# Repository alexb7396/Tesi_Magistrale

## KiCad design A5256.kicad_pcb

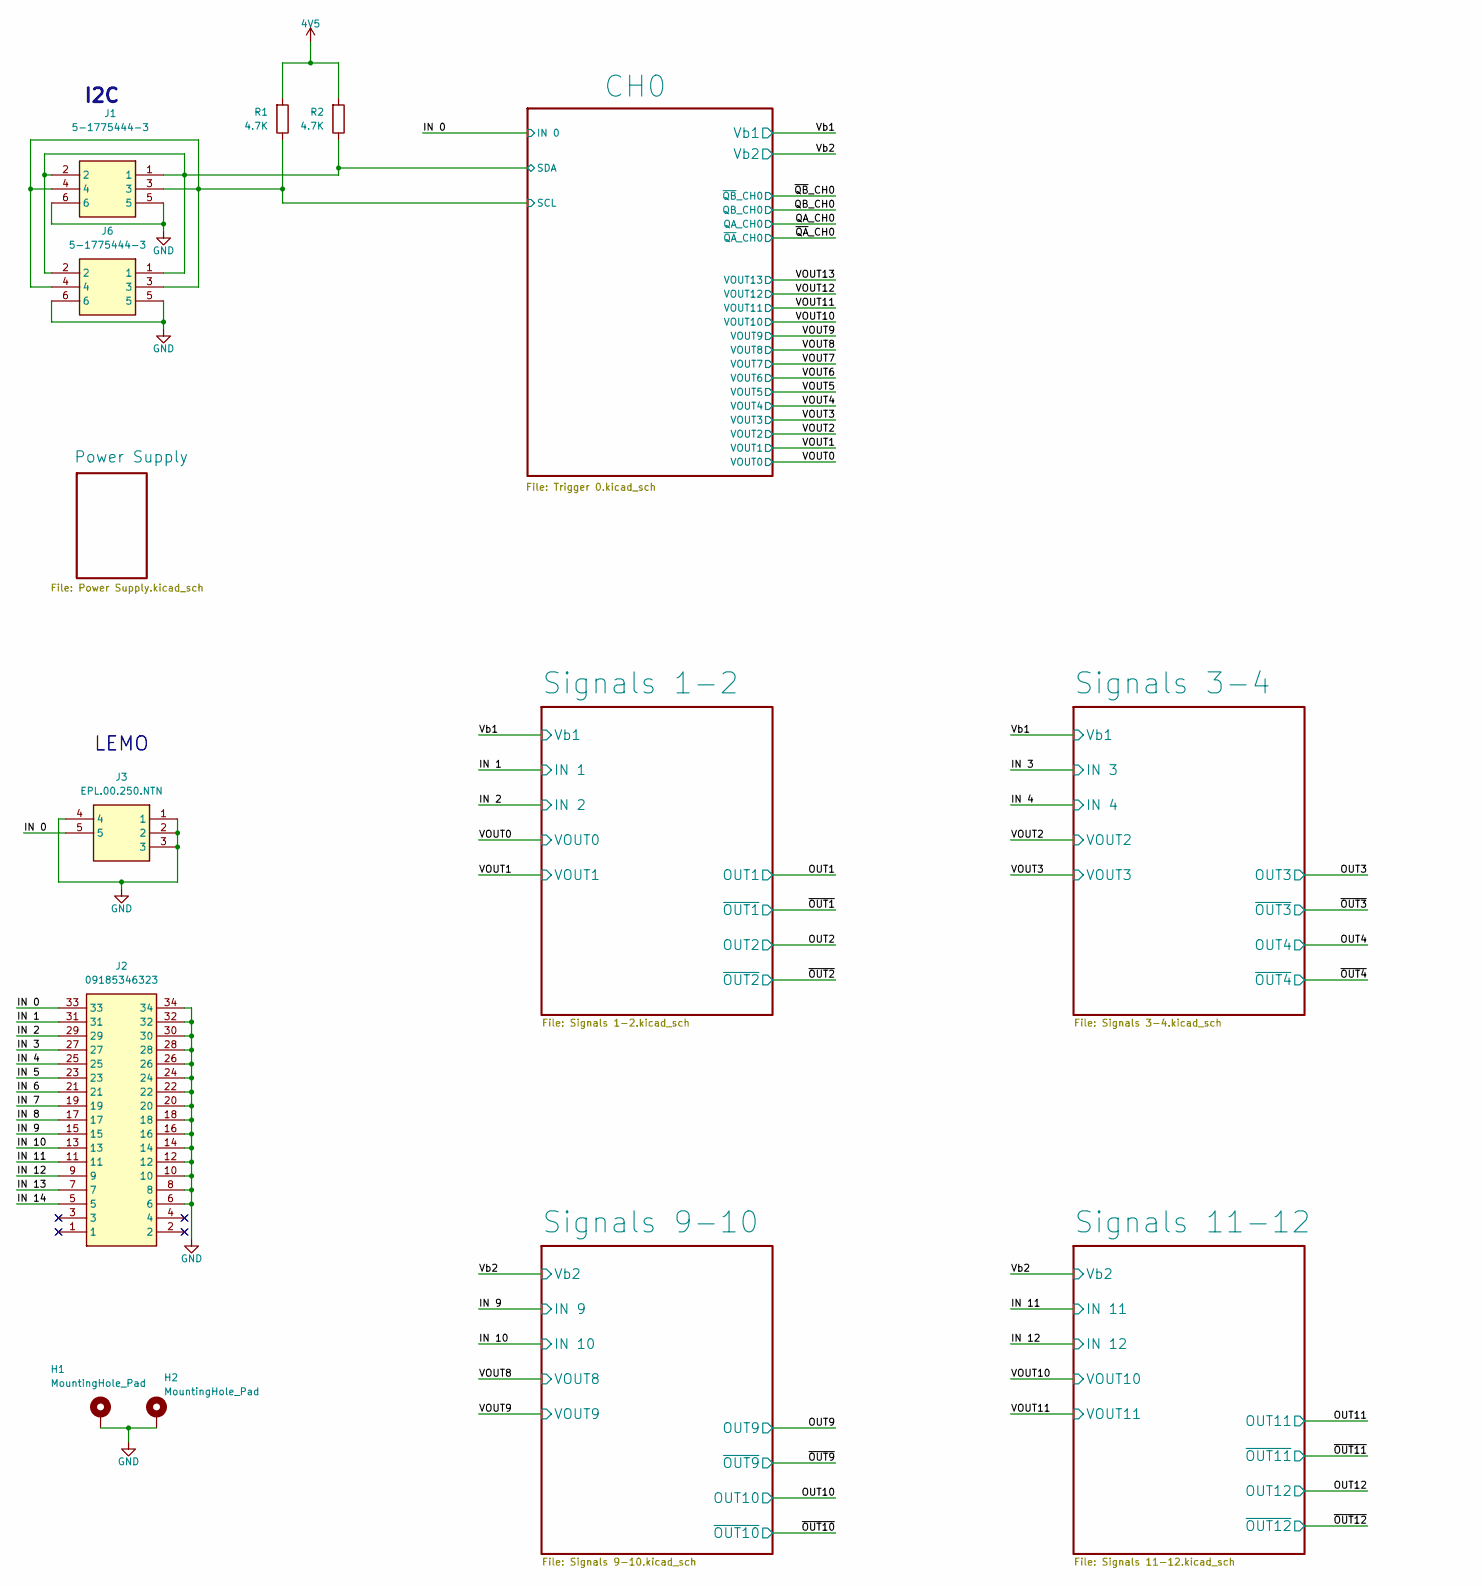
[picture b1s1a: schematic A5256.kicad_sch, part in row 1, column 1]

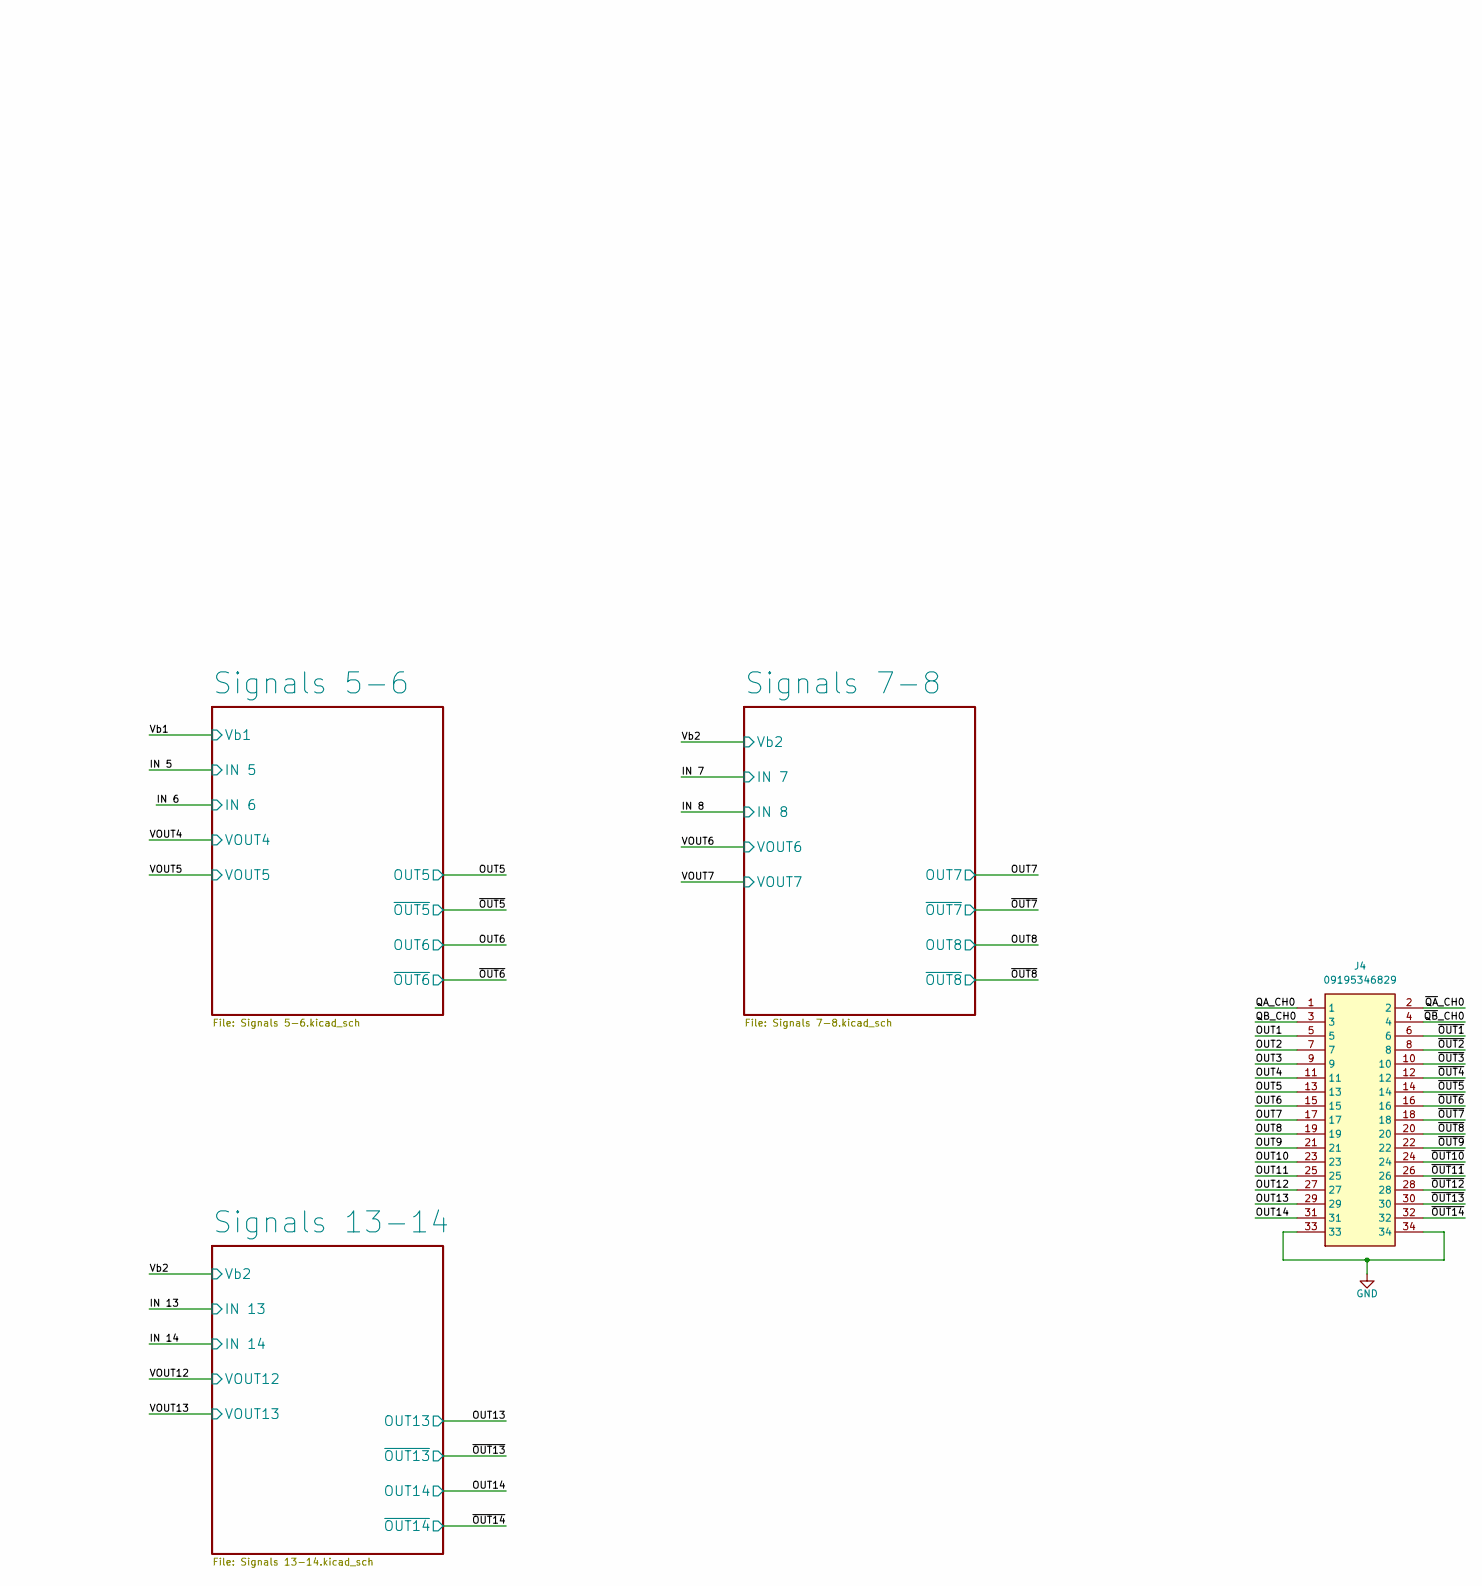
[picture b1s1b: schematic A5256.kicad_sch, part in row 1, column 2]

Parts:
H1, H2: MountingHole_Pad; MountingHole_3mm_Pad_TopBottom
J1, J6: 5-1775444-3; 517754443; Mouser Part Number 571-5-1775444-3
J2: 09185346323; Mouser Part Number 617-09-18-534-6323
J3: EPL.00.250.NTN; LEMO-EPA.00.250.DTN; Mouser Part Number 736-EPL00250NTN
J4: 09195346829; 2x17 Connector; Mouser Part Number 617-09195346829
R1, R2: 4.7K; R_0603_1608Metric_Pad0.98x0.95mm_HandSolder

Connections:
4V5: R1.2, R2.2; also elsewhere on the board
/CH0/SCL: J1.3, J1.4, J6.3, J6.4, R1.1; also elsewhere on the board
/CH0/SDA: J1.1, J1.2, J6.1, J6.2, R2.1; also elsewhere on the board
/IN 0: J2.33, J3.5; also elsewhere on the board
/IN 1: J2.31; also elsewhere on the board
/IN 2: J2.29; also elsewhere on the board
/IN 3: J2.27; also elsewhere on the board
/IN 4: J2.25; also elsewhere on the board
/IN 5: J2.23; also elsewhere on the board
/IN 6: J2.21; also elsewhere on the board
/IN 7: J2.19; also elsewhere on the board
/IN 8: J2.17; also elsewhere on the board
/IN 9: J2.15; also elsewhere on the board
/IN 10: J2.13; also elsewhere on the board
/IN 11: J2.11; also elsewhere on the board
/IN 12: J2.9; also elsewhere on the board
/IN 13: J2.7; also elsewhere on the board
/IN 14: J2.5; also elsewhere on the board
/OUT1: J4.5; also elsewhere on the board
/OUT2: J4.7; also elsewhere on the board
/OUT3: J4.9; also elsewhere on the board
/OUT4: J4.11; also elsewhere on the board
/OUT5: J4.13; also elsewhere on the board
/OUT6: J4.15; also elsewhere on the board
/OUT7: J4.17; also elsewhere on the board
/OUT8: J4.19; also elsewhere on the board
/OUT9: J4.21; also elsewhere on the board
/OUT10: J4.23; also elsewhere on the board
/OUT11: J4.25; also elsewhere on the board
/OUT12: J4.27; also elsewhere on the board
/OUT13: J4.29; also elsewhere on the board
/OUT14: J4.31; also elsewhere on the board
/QA_CH0: J4.1; also elsewhere on the board
/QB_CH0: J4.3; also elsewhere on the board
/~OUT1: J4.6; also elsewhere on the board
/~OUT2: J4.8; also elsewhere on the board
/~OUT3: J4.10; also elsewhere on the board
/~OUT4: J4.12; also elsewhere on the board
/~OUT5: J4.14; also elsewhere on the board
/~OUT6: J4.16; also elsewhere on the board
/~OUT7: J4.18; also elsewhere on the board
/~OUT8: J4.20; also elsewhere on the board
/~OUT9: J4.22; also elsewhere on the board
/~OUT10: J4.24; also elsewhere on the board
/~OUT11: J4.26; also elsewhere on the board
/~OUT12: J4.28; also elsewhere on the board
/~OUT13: J4.30; also elsewhere on the board
/~OUT14: J4.32; also elsewhere on the board
/~QA_CH0: J4.2; also elsewhere on the board
/~QB_CH0: J4.4; also elsewhere on the board
GND: H1.1, H2.1, J1.5, J1.6, J2.6, J2.8, J2.10, J2.12, J2.14, J2.16, J2.18, J2.20, J2.22, J2.24, J2.26, J2.28, J2.30, J2.32, J2.34, J3.1, J3.2, J3.3, J3.4, J4.33, J4.34, J6.5, J6.6; also elsewhere on the board

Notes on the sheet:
I2C
LEMO

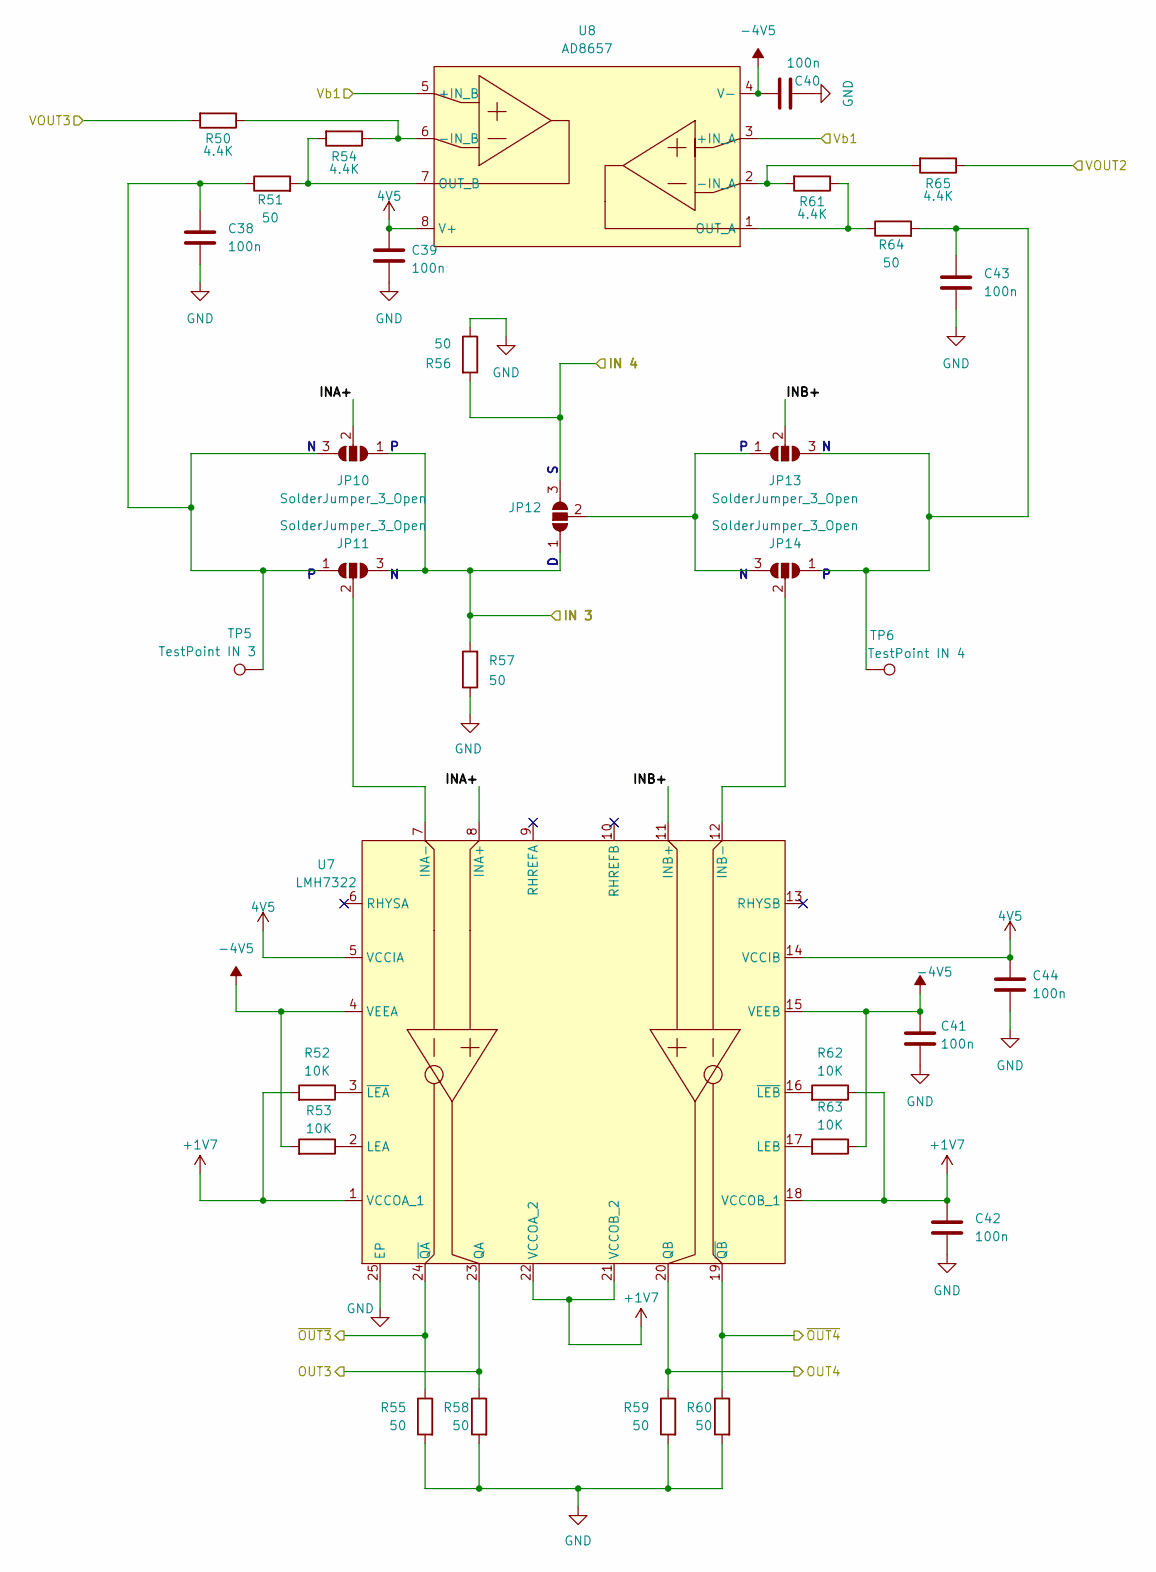
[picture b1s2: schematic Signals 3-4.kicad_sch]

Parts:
C38, C39, C40, C41, C42, C43, C44: 100n; C_0603_1608Metric_Pad1.08x0.95mm_HandSolder
JP10, JP11, JP12, JP13, JP14: SolderJumper_3_Open; SolderJumper-3_P1.3mm_Open_RoundedPad1.0x1.5mm_NumberLabels
R50, R54, R61, R65: 4.4K; R_0603_1608Metric_Pad0.98x0.95mm_HandSolder
R51, R55, R56, R57, R58, R59, R60, R64: 50; R_0603_1608Metric_Pad0.98x0.95mm_HandSolder
R52, R53, R62, R63: 10K; R_0603_1608Metric_Pad0.98x0.95mm_HandSolder
TP5: TestPoint IN 3; TestPoint_Pad_D1.0mm
TP6: TestPoint IN 4; TestPoint_Pad_D1.0mm
U7: LMH7322; QFN50P400X400X80-25N
U8: AD8657; SOP65P490X110-8N

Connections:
4V5: C39.1, C44.1, U7.5 (VCCIA), U7.14 (VCCIB), U8.8 (V+); also elsewhere on the board
+1V7: C42.1, R52.2, R62.1, U7.1 (VCCOA_1), U7.18 (VCCOB_1), U7.21 (VCCOB_2), U7.22 (VCCOA_2); also elsewhere on the board
-4V5: C40.1, C41.1, R53.2, R63.1, U7.4 (VEEA), U7.15 (VEEB), U8.4 (V-); also elsewhere on the board
/IN 3: JP10.1 (A), JP11.3 (B), JP12.1 (A), R57.2; also elsewhere on the board
/IN 4: JP12.3 (B), R56.2; also elsewhere on the board
/OUT3: R58.1, U7.23 (QA); also elsewhere on the board
/OUT4: R59.1, U7.20 (QB); also elsewhere on the board
/Signals 3-4/INA+: JP10.2 (C), U7.8 (INA+)
/Signals 3-4/INB+: JP13.2 (C), U7.11 (INB+)
/VOUT2: R65.1; also elsewhere on the board
/VOUT3: R50.2; also elsewhere on the board
/Vb1: U8.3 (+IN_A), U8.5 (+IN_B); also elsewhere on the board
/~OUT3: R55.1, U7.24 (~QA); also elsewhere on the board
/~OUT4: R60.1, U7.19 (~QB); also elsewhere on the board
GND: C38.2, C39.2, C40.2, C41.2, C42.2, C43.2, C44.2, R55.2, R56.1, R57.1, R58.2, R59.2, R60.2, U7.25 (EP); also elsewhere on the board
unnamed: C38.1, JP10.3 (B), JP11.1 (A), R51.1, TP5.1
unnamed: JP11.2 (C), U7.7 (INA-)
unnamed: JP12.2 (C), JP13.1 (A), JP14.3 (B)
unnamed: C43.1, JP13.3 (B), JP14.1 (A), R64.2, TP6.1
unnamed: JP14.2 (C), U7.12 (INB-)
unnamed: R53.1, U7.2 (LEA)
unnamed: R63.2, U7.17 (LEB)
unnamed: R52.1, U7.3 (~LEA)
unnamed: R62.2, U7.16 (~LEB)
unnamed: R61.2, R65.2, U8.2 (-IN_A)
unnamed: R50.1, R54.1, U8.6 (-IN_B)
unnamed: R61.1, R64.1, U8.1 (OUT_A)
unnamed: R51.2, R54.2, U8.7 (OUT_B)

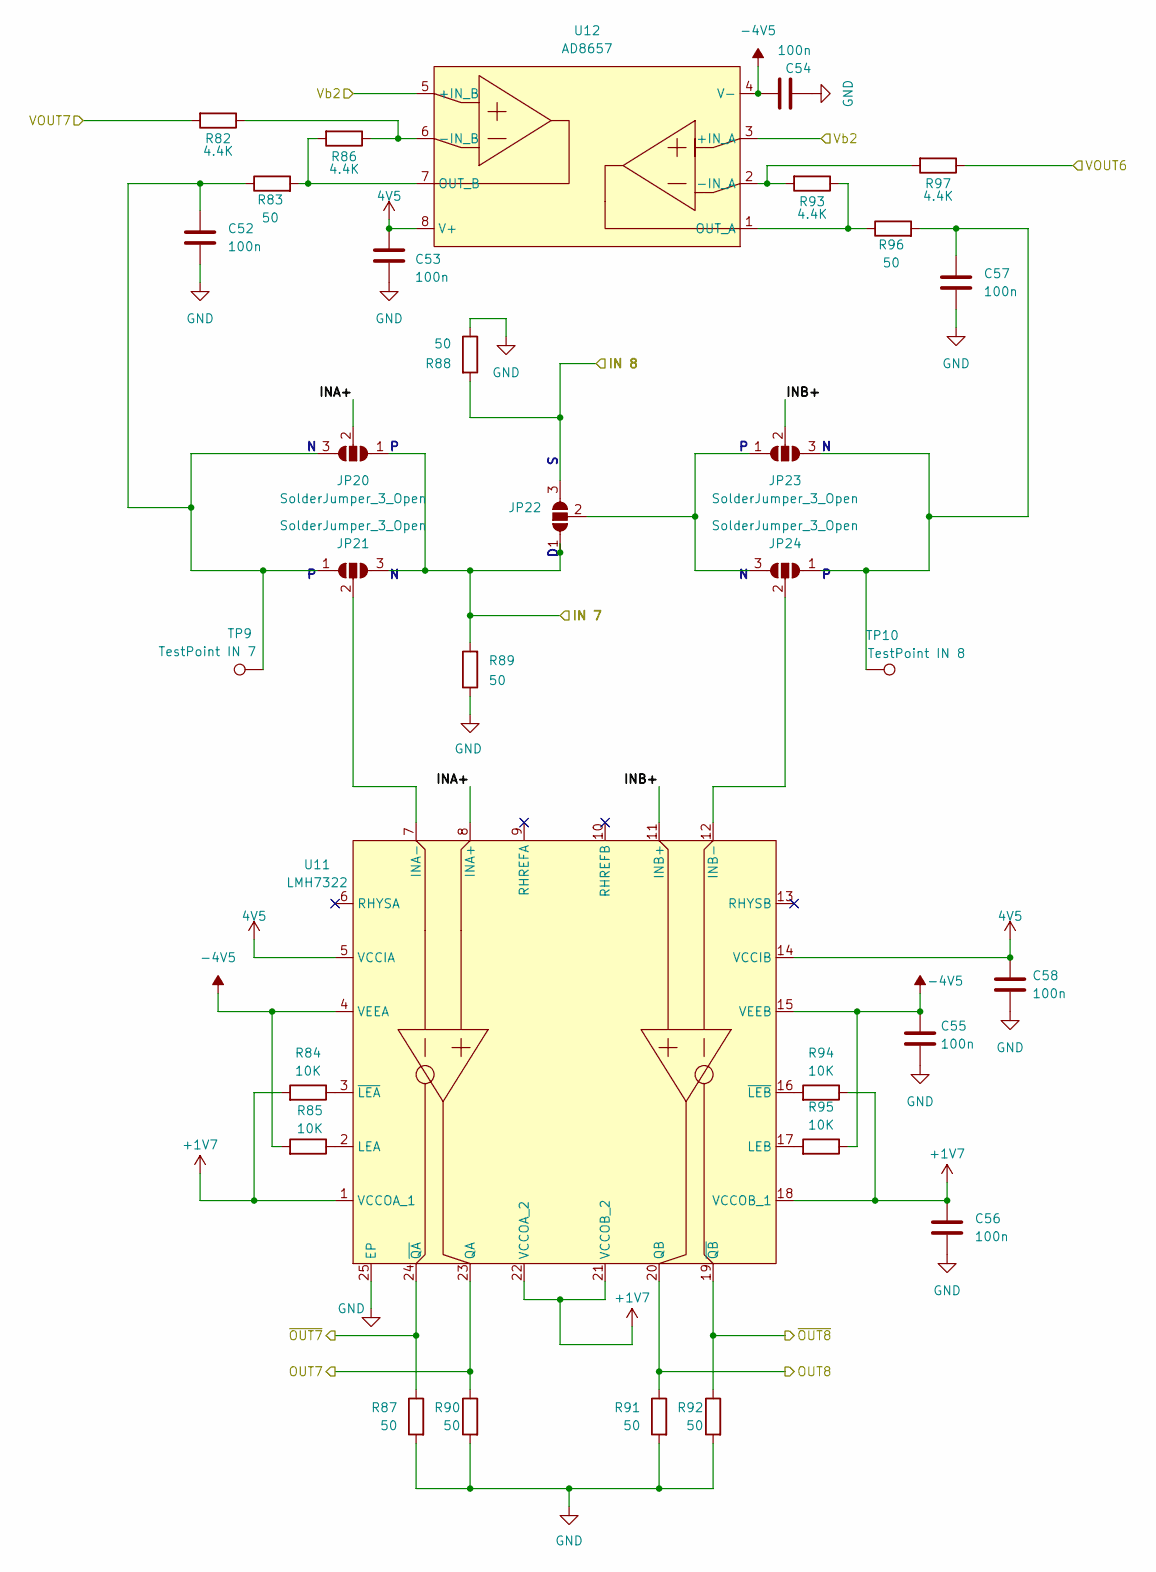
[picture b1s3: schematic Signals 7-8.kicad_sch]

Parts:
C52, C53, C54, C55, C56, C57, C58: 100n; C_0603_1608Metric_Pad1.08x0.95mm_HandSolder
JP20, JP21, JP22, JP23, JP24: SolderJumper_3_Open; SolderJumper-3_P1.3mm_Open_RoundedPad1.0x1.5mm_NumberLabels
R82, R86, R93, R97: 4.4K; R_0603_1608Metric_Pad0.98x0.95mm_HandSolder
R83, R87, R88, R89, R90, R91, R92, R96: 50; R_0603_1608Metric_Pad0.98x0.95mm_HandSolder
R84, R85, R94, R95: 10K; R_0603_1608Metric_Pad0.98x0.95mm_HandSolder
TP9: TestPoint IN 7; TestPoint_Pad_D1.0mm
TP10: TestPoint IN 8; TestPoint_Pad_D1.0mm
U11: LMH7322; QFN50P400X400X80-25N
U12: AD8657; SOP65P490X110-8N

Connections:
4V5: C53.1, C58.1, U11.5 (VCCIA), U11.14 (VCCIB), U12.8 (V+); also elsewhere on the board
+1V7: C56.1, R84.2, R94.1, U11.1 (VCCOA_1), U11.18 (VCCOB_1), U11.21 (VCCOB_2), U11.22 (VCCOA_2); also elsewhere on the board
-4V5: C54.1, C55.1, R85.2, R95.1, U11.4 (VEEA), U11.15 (VEEB), U12.4 (V-); also elsewhere on the board
/IN 7: JP20.1 (A), JP21.3 (B), JP22.1 (A), R89.2; also elsewhere on the board
/IN 8: JP22.3 (B), R88.2; also elsewhere on the board
/OUT7: R90.1, U11.23 (QA); also elsewhere on the board
/OUT8: R91.1, U11.20 (QB); also elsewhere on the board
/Signals 7-8/INA+: JP20.2 (C), U11.8 (INA+)
/Signals 7-8/INB+: JP23.2 (C), U11.11 (INB+)
/VOUT6: R97.1; also elsewhere on the board
/VOUT7: R82.2; also elsewhere on the board
/Vb2: U12.3 (+IN_A), U12.5 (+IN_B); also elsewhere on the board
/~OUT7: R87.1, U11.24 (~QA); also elsewhere on the board
/~OUT8: R92.1, U11.19 (~QB); also elsewhere on the board
GND: C52.2, C53.2, C54.2, C55.2, C56.2, C57.2, C58.2, R87.2, R88.1, R89.1, R90.2, R91.2, R92.2, U11.25 (EP); also elsewhere on the board
unnamed: C52.1, JP20.3 (B), JP21.1 (A), R83.1, TP9.1
unnamed: JP21.2 (C), U11.7 (INA-)
unnamed: JP22.2 (C), JP23.1 (A), JP24.3 (B)
unnamed: C57.1, JP23.3 (B), JP24.1 (A), R96.2, TP10.1
unnamed: JP24.2 (C), U11.12 (INB-)
unnamed: R85.1, U11.2 (LEA)
unnamed: R95.2, U11.17 (LEB)
unnamed: R84.1, U11.3 (~LEA)
unnamed: R94.2, U11.16 (~LEB)
unnamed: R93.2, R97.2, U12.2 (-IN_A)
unnamed: R82.1, R86.1, U12.6 (-IN_B)
unnamed: R93.1, R96.1, U12.1 (OUT_A)
unnamed: R83.2, R86.2, U12.7 (OUT_B)

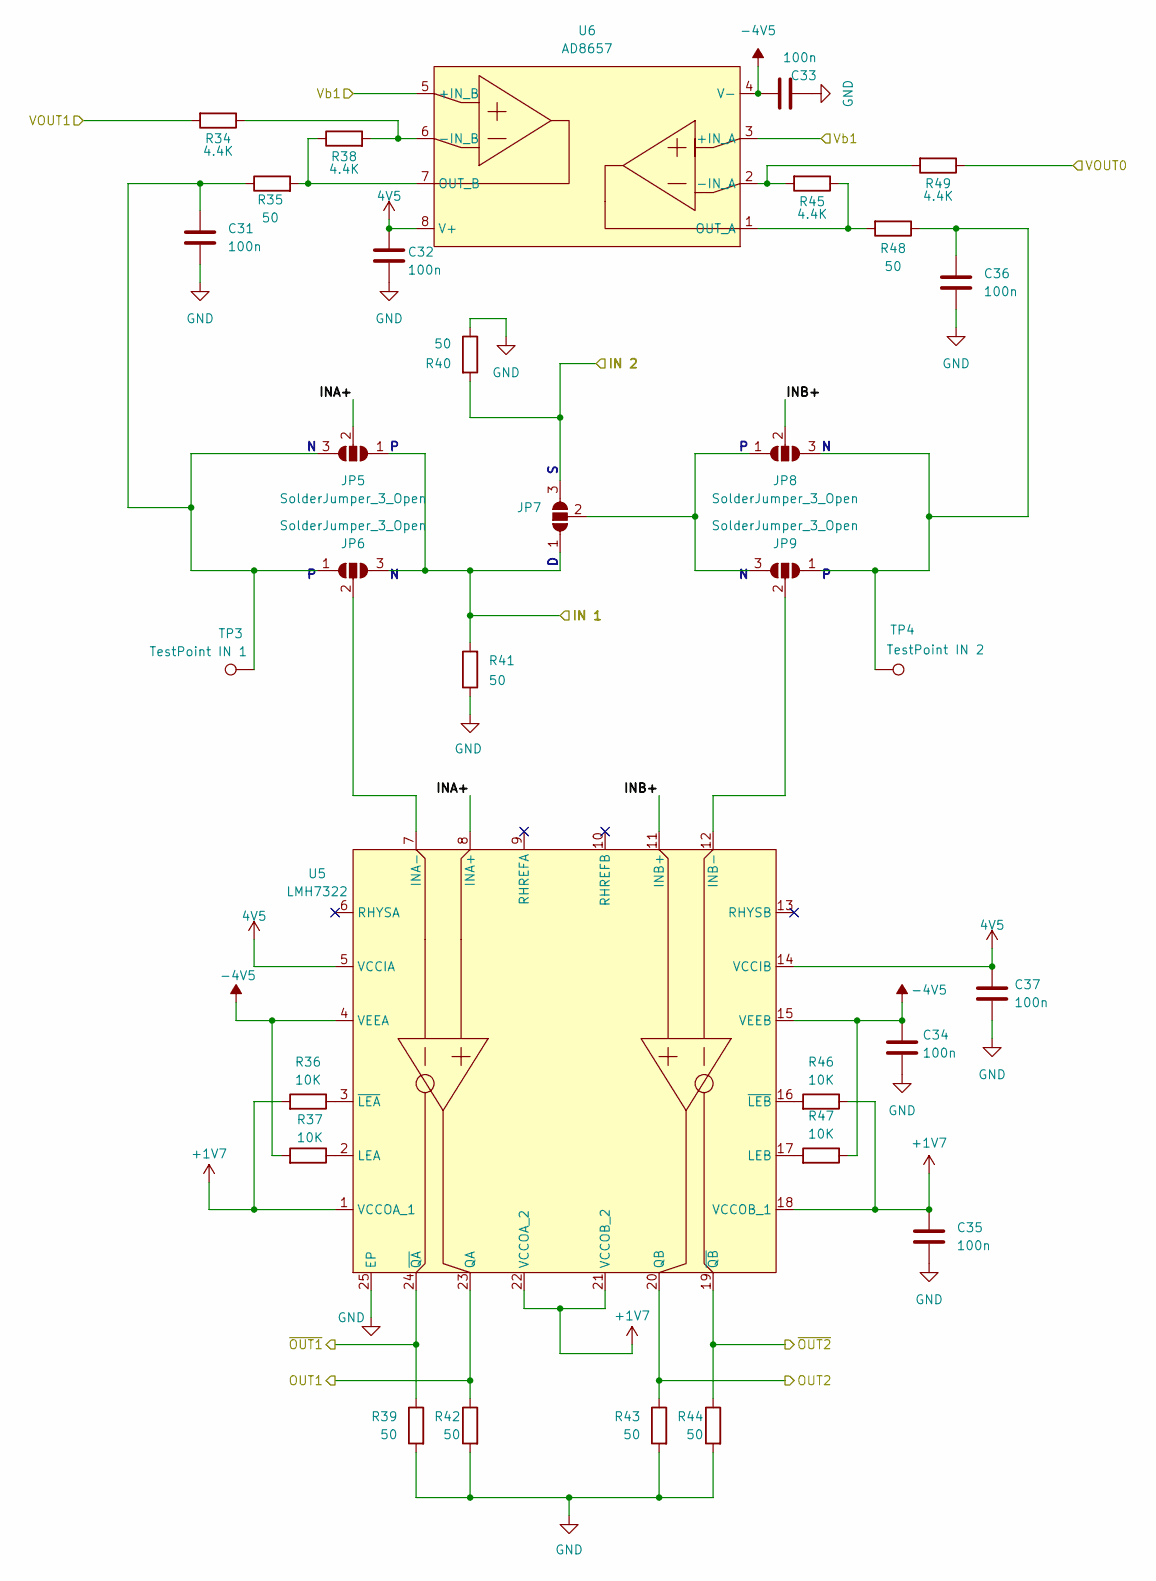
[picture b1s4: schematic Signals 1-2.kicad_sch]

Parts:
C31, C32, C33, C34, C35, C36, C37: 100n; C_0603_1608Metric_Pad1.08x0.95mm_HandSolder
JP5, JP6, JP7, JP8, JP9: SolderJumper_3_Open; SolderJumper-3_P1.3mm_Open_RoundedPad1.0x1.5mm_NumberLabels
R34, R38, R45, R49: 4.4K; R_0603_1608Metric_Pad0.98x0.95mm_HandSolder
R35, R39, R40, R41, R42, R43, R44, R48: 50; R_0603_1608Metric_Pad0.98x0.95mm_HandSolder
R36, R37, R46, R47: 10K; R_0603_1608Metric_Pad0.98x0.95mm_HandSolder
TP3: TestPoint IN 1; TestPoint_Pad_D1.0mm
TP4: TestPoint IN 2; TestPoint_Pad_D1.0mm
U5: LMH7322; QFN50P400X400X80-25N
U6: AD8657; SOP65P490X110-8N

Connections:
4V5: C32.1, C37.1, U5.5 (VCCIA), U5.14 (VCCIB), U6.8 (V+); also elsewhere on the board
+1V7: C35.1, R36.2, R46.1, U5.1 (VCCOA_1), U5.18 (VCCOB_1), U5.21 (VCCOB_2), U5.22 (VCCOA_2); also elsewhere on the board
-4V5: C33.1, C34.1, R37.2, R47.1, U5.4 (VEEA), U5.15 (VEEB), U6.4 (V-); also elsewhere on the board
/IN 1: JP5.1 (A), JP6.3 (B), JP7.1 (A), R41.2; also elsewhere on the board
/IN 2: JP7.3 (B), R40.2; also elsewhere on the board
/OUT1: R42.1, U5.23 (QA); also elsewhere on the board
/OUT2: R43.1, U5.20 (QB); also elsewhere on the board
/Signals 1-2/INA+: JP5.2 (C), U5.8 (INA+)
/Signals 1-2/INB+: JP8.2 (C), U5.11 (INB+)
/VOUT0: R49.1; also elsewhere on the board
/VOUT1: R34.2; also elsewhere on the board
/Vb1: U6.3 (+IN_A), U6.5 (+IN_B); also elsewhere on the board
/~OUT1: R39.1, U5.24 (~QA); also elsewhere on the board
/~OUT2: R44.1, U5.19 (~QB); also elsewhere on the board
GND: C31.2, C32.2, C33.2, C34.2, C35.2, C36.2, C37.2, R39.2, R40.1, R41.1, R42.2, R43.2, R44.2, U5.25 (EP); also elsewhere on the board
unnamed: C31.1, JP5.3 (B), JP6.1 (A), R35.1, TP3.1
unnamed: JP6.2 (C), U5.7 (INA-)
unnamed: JP7.2 (C), JP8.1 (A), JP9.3 (B)
unnamed: C36.1, JP8.3 (B), JP9.1 (A), R48.1, TP4.1
unnamed: JP9.2 (C), U5.12 (INB-)
unnamed: R37.1, U5.2 (LEA)
unnamed: R47.2, U5.17 (LEB)
unnamed: R36.1, U5.3 (~LEA)
unnamed: R46.2, U5.16 (~LEB)
unnamed: R45.2, R49.2, U6.2 (-IN_A)
unnamed: R34.1, R38.2, U6.6 (-IN_B)
unnamed: R45.1, R48.2, U6.1 (OUT_A)
unnamed: R35.2, R38.1, U6.7 (OUT_B)

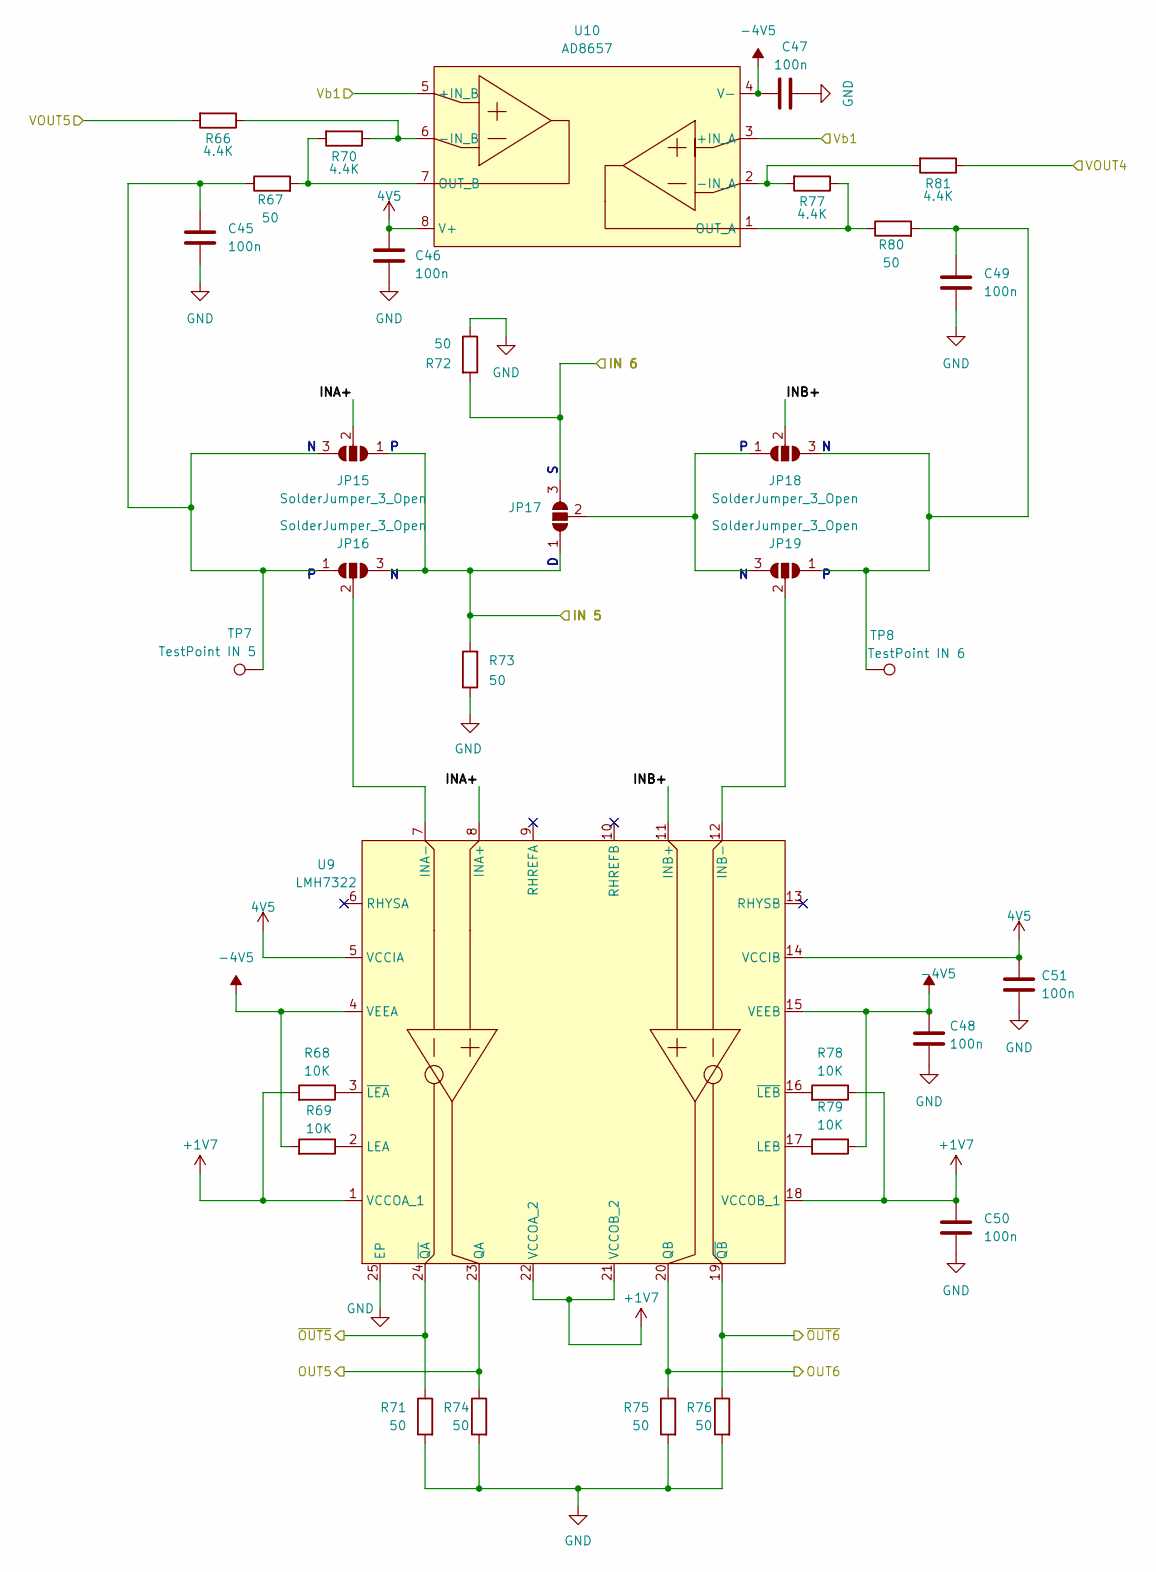
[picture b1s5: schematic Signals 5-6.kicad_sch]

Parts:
C45, C46, C47, C48, C49, C50, C51: 100n; C_0603_1608Metric_Pad1.08x0.95mm_HandSolder
JP15, JP16, JP17, JP18, JP19: SolderJumper_3_Open; SolderJumper-3_P1.3mm_Open_RoundedPad1.0x1.5mm_NumberLabels
R66, R70, R77, R81: 4.4K; R_0603_1608Metric_Pad0.98x0.95mm_HandSolder
R67, R71, R72, R73, R74, R75, R76, R80: 50; R_0603_1608Metric_Pad0.98x0.95mm_HandSolder
R68, R69, R78, R79: 10K; R_0603_1608Metric_Pad0.98x0.95mm_HandSolder
TP7: TestPoint IN 5; TestPoint_Pad_D1.0mm
TP8: TestPoint IN 6; TestPoint_Pad_D1.0mm
U9: LMH7322; QFN50P400X400X80-25N
U10: AD8657; SOP65P490X110-8N

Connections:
4V5: C46.1, C51.1, U9.5 (VCCIA), U9.14 (VCCIB), U10.8 (V+); also elsewhere on the board
+1V7: C50.1, R68.2, R78.1, U9.1 (VCCOA_1), U9.18 (VCCOB_1), U9.21 (VCCOB_2), U9.22 (VCCOA_2); also elsewhere on the board
-4V5: C47.1, C48.1, R69.2, R79.1, U9.4 (VEEA), U9.15 (VEEB), U10.4 (V-); also elsewhere on the board
/IN 5: JP15.1 (A), JP16.3 (B), JP17.1 (A), R73.2; also elsewhere on the board
/IN 6: JP17.3 (B), R72.2; also elsewhere on the board
/OUT5: R74.1, U9.23 (QA); also elsewhere on the board
/OUT6: R75.1, U9.20 (QB); also elsewhere on the board
/Signals 5-6/INA+: JP15.2 (C), U9.8 (INA+)
/Signals 5-6/INB+: JP18.2 (C), U9.11 (INB+)
/VOUT4: R81.1; also elsewhere on the board
/VOUT5: R66.2; also elsewhere on the board
/Vb1: U10.3 (+IN_A), U10.5 (+IN_B); also elsewhere on the board
/~OUT5: R71.1, U9.24 (~QA); also elsewhere on the board
/~OUT6: R76.1, U9.19 (~QB); also elsewhere on the board
GND: C45.2, C46.2, C47.2, C48.2, C49.2, C50.2, C51.2, R71.2, R72.1, R73.1, R74.2, R75.2, R76.2, U9.25 (EP); also elsewhere on the board
unnamed: C45.1, JP15.3 (B), JP16.1 (A), R67.1, TP7.1
unnamed: JP16.2 (C), U9.7 (INA-)
unnamed: JP17.2 (C), JP18.1 (A), JP19.3 (B)
unnamed: C49.1, JP18.3 (B), JP19.1 (A), R80.2, TP8.1
unnamed: JP19.2 (C), U9.12 (INB-)
unnamed: R69.1, U9.2 (LEA)
unnamed: R79.2, U9.17 (LEB)
unnamed: R68.1, U9.3 (~LEA)
unnamed: R78.2, U9.16 (~LEB)
unnamed: R77.2, R81.2, U10.2 (-IN_A)
unnamed: R66.1, R70.1, U10.6 (-IN_B)
unnamed: R77.1, R80.1, U10.1 (OUT_A)
unnamed: R67.2, R70.2, U10.7 (OUT_B)

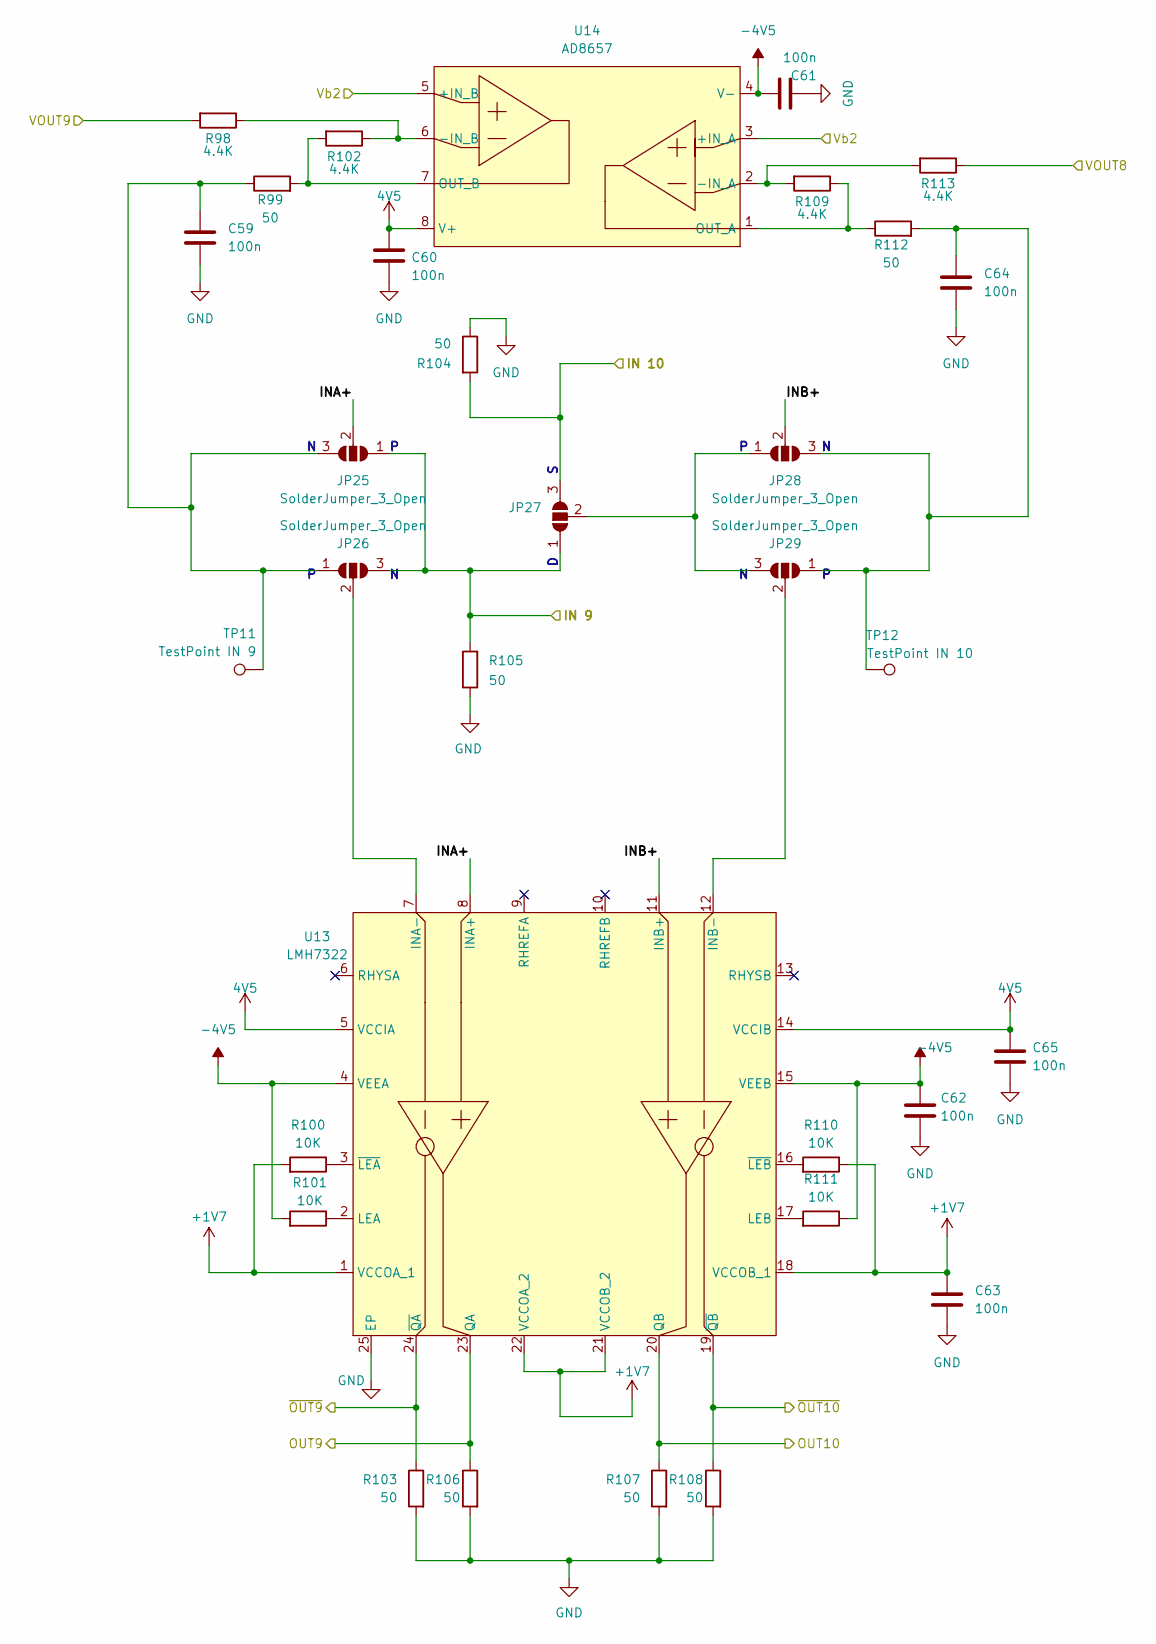
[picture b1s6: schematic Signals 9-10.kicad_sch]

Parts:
C59, C60, C61, C62, C63, C64, C65: 100n; C_0603_1608Metric_Pad1.08x0.95mm_HandSolder
JP25, JP26, JP27, JP28, JP29: SolderJumper_3_Open; SolderJumper-3_P1.3mm_Open_RoundedPad1.0x1.5mm_NumberLabels
R98, R102, R109, R113: 4.4K; R_0603_1608Metric_Pad0.98x0.95mm_HandSolder
R99, R103, R104, R105, R106, R107, R108, R112: 50; R_0603_1608Metric_Pad0.98x0.95mm_HandSolder
R100, R101, R110, R111: 10K; R_0603_1608Metric_Pad0.98x0.95mm_HandSolder
TP11: TestPoint IN 9; TestPoint_Pad_D1.0mm
TP12: TestPoint IN 10; TestPoint_Pad_D1.0mm
U13: LMH7322; QFN50P400X400X80-25N
U14: AD8657; SOP65P490X110-8N

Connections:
4V5: C60.1, C65.1, U13.5 (VCCIA), U13.14 (VCCIB), U14.8 (V+); also elsewhere on the board
+1V7: C63.1, R100.2, R110.1, U13.1 (VCCOA_1), U13.18 (VCCOB_1), U13.21 (VCCOB_2), U13.22 (VCCOA_2); also elsewhere on the board
-4V5: C61.1, C62.1, R101.2, R111.1, U13.4 (VEEA), U13.15 (VEEB), U14.4 (V-); also elsewhere on the board
/IN 9: JP25.1 (A), JP26.3 (B), JP27.1 (A), R105.2; also elsewhere on the board
/IN 10: JP27.3 (B), R104.2; also elsewhere on the board
/OUT9: R106.1, U13.23 (QA); also elsewhere on the board
/OUT10: R107.1, U13.20 (QB); also elsewhere on the board
/Signals 9-10/INA+: JP25.2 (C), U13.8 (INA+)
/Signals 9-10/INB+: JP28.2 (C), U13.11 (INB+)
/VOUT8: R113.1; also elsewhere on the board
/VOUT9: R98.2; also elsewhere on the board
/Vb2: U14.3 (+IN_A), U14.5 (+IN_B); also elsewhere on the board
/~OUT9: R103.1, U13.24 (~QA); also elsewhere on the board
/~OUT10: R108.1, U13.19 (~QB); also elsewhere on the board
GND: C59.2, C60.2, C61.2, C62.2, C63.2, C64.2, C65.2, R103.2, R104.1, R105.1, R106.2, R107.2, R108.2, U13.25 (EP); also elsewhere on the board
unnamed: C59.1, JP25.3 (B), JP26.1 (A), R99.1, TP11.1
unnamed: JP26.2 (C), U13.7 (INA-)
unnamed: JP27.2 (C), JP28.1 (A), JP29.3 (B)
unnamed: C64.1, JP28.3 (B), JP29.1 (A), R112.2, TP12.1
unnamed: JP29.2 (C), U13.12 (INB-)
unnamed: R101.1, U13.2 (LEA)
unnamed: R111.2, U13.17 (LEB)
unnamed: R100.1, U13.3 (~LEA)
unnamed: R110.2, U13.16 (~LEB)
unnamed: R109.2, R113.2, U14.2 (-IN_A)
unnamed: R98.1, R102.1, U14.6 (-IN_B)
unnamed: R109.1, R112.1, U14.1 (OUT_A)
unnamed: R99.2, R102.2, U14.7 (OUT_B)
